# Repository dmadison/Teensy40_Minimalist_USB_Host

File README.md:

# Teensy 4.0 Minimalist USB Host Shield

This repository contains the KiCAD 6 board files for the [Teensy 4.0 minimalist USB host shield](https://www.partsnotincluded.com/teensy-4-0-minimalist-usb-host-shield). The shield is designed to connect to the underside of the Teensy 4.0 board and provide a safe and stable USB-A host port in a small and lightweight size.

The Teensy board needs to be soldered to 0.1" male headers. It can then be mated to the shield with 0.1" female headers and pogo pins, or soldered directly using enamel wire to connect to the data pads on the underside of the board.

For pogo pins, see the [PJRC Teensy 4.0 breakout board](https://www.pjrc.com/breakout-board-for-teensy-4-0/) page for reference. For my own boards I used 12 mm pogo pins purchased from RTLECS on AliExpress.

Generated gerbers and bill of materials can be found on the [releases](../../releases/latest) page.

## License

The KiCAD project files including the schematic, PCB design, symbols, and most footprints are released in the public domain with no rights reserved.

The [Parts Not Included](https://www.partsnotincluded.com/) logo, included on the bottom of the shield, is copyrighted. It may be reproduced as a silkscreen graphic in this project and its derivatives without modification.

Included images are licensed under the [CC BY-NC-ND 4.0 license](https://creativecommons.org/licenses/by-nc-nd/4.0/). Attribution should be to Dave Madison ([@dmadison](https://github.com/dmadison)).

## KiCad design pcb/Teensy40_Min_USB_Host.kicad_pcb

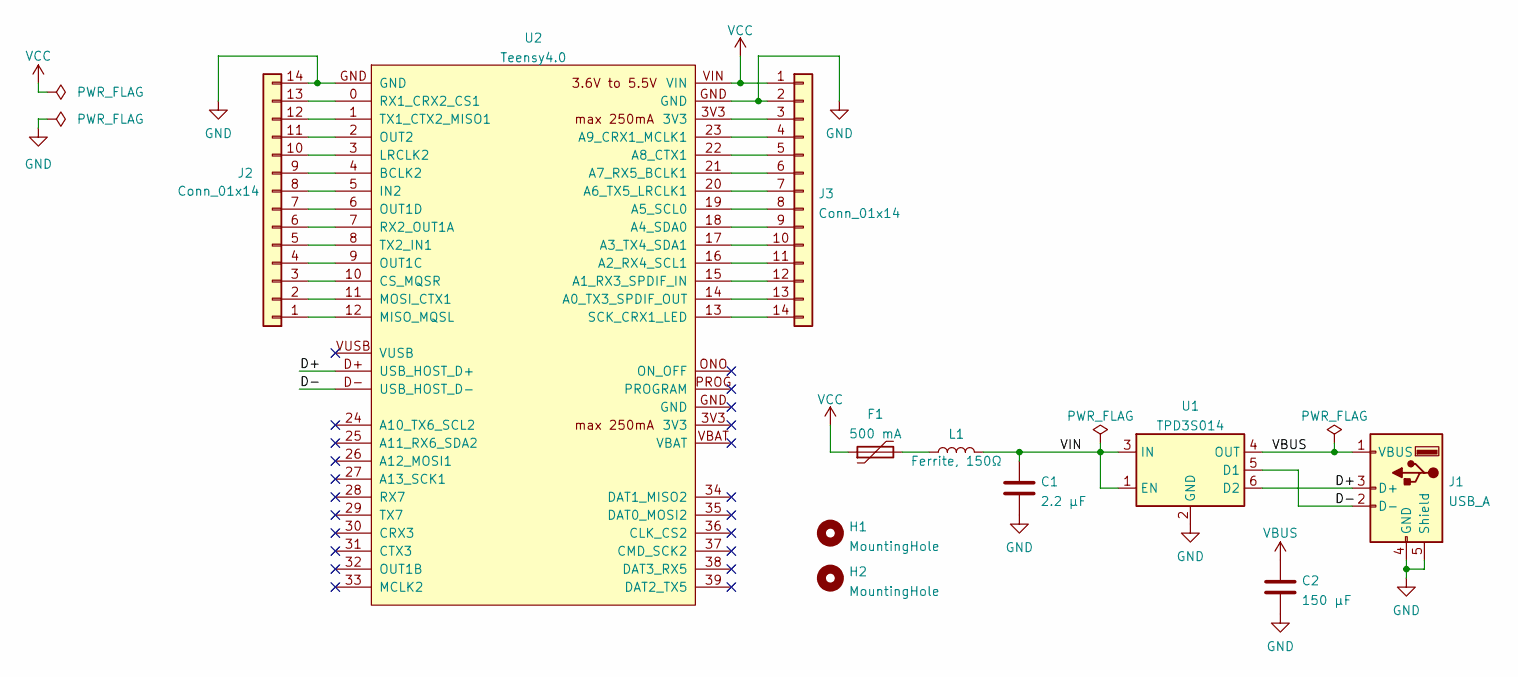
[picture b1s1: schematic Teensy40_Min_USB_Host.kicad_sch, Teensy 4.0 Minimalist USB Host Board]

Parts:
C1: 2.2 µF; C_0805_2012Metric; DigiKey Product Number 445-1420-1-ND - Cut Tape
C2: 150 µF; CP_EIA-3216-10_Kemet-I; DigiKey Product Number 478-6250-1-ND
F1: 500 mA; Fuse_0805_2012Metric; DigiKey Product Number 283-PTS08056V050CT-ND
H1, H2: MountingHole; MountingHole_3.2mm
J1: USB_A; USB_A_Stewart_SS-52100-001_Horizontal; DigiKey Product Number 380-1412-ND
J2, J3: Conn_01x14; PinHeader_1x14_P2.54mm_Vertical; DigiKey Product Number S1011EC-14-ND
L1: Ferrite, 150Ω; L_0805_2012Metric; DigiKey Product Number MH2029-151YCT-ND
U1: TPD3S014; SOT-23-6; DigiKey Product Number 296-44163-1-ND
U2: Teensy4.0; Teensy40_USB; DigiKey Product Number 1568-DEV-15583-ND

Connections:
/D+: J1.3 (D+), U1.6 (D2), U2.D+ (USB_HOST_D+)
/D-: J1.2 (D-), U1.5 (D1), U2.D- (USB_HOST_D-)
/VIN: C1.1, L1.2, U1.1 (EN), U1.3 (IN)
GND: C1.2, C2.2, J1.4 (GND), J1.5 (Shield), J2.14, J3.2, U1.2 (GND), U2.GND
unnamed: F1.2, L1.1
unnamed: J2.1, U2.12 (MISO_MQSL)
unnamed: J2.2, U2.11 (MOSI_CTX1)
unnamed: J2.3, U2.10 (CS_MQSR)
unnamed: J2.4, U2.9 (OUT1C)
unnamed: J2.5, U2.8 (TX2_IN1)
unnamed: J2.6, U2.7 (RX2_OUT1A)
unnamed: J2.7, U2.6 (OUT1D)
unnamed: J2.8, U2.5 (IN2)
unnamed: J2.9, U2.4 (BCLK2)
unnamed: J2.10, U2.3 (LRCLK2)
unnamed: J2.11, U2.2 (OUT2)
unnamed: J2.12, U2.1 (TX1_CTX2_MISO1)
unnamed: J2.13, U2.0 (RX1_CRX2_CS1)
unnamed: J3.3, U2.3V3
unnamed: J3.4, U2.23 (A9_CRX1_MCLK1)
unnamed: J3.5, U2.22 (A8_CTX1)
unnamed: J3.6, U2.21 (A7_RX5_BCLK1)
unnamed: J3.7, U2.20 (A6_TX5_LRCLK1)
unnamed: J3.8, U2.19 (A5_SCL0)
unnamed: J3.9, U2.18 (A4_SDA0)
unnamed: J3.10, U2.17 (A3_TX4_SDA1)
unnamed: J3.11, U2.16 (A2_RX4_SCL1)
unnamed: J3.12, U2.15 (A1_RX3_SPDIF_IN)
unnamed: J3.13, U2.14 (A0_TX3_SPDIF_OUT)
unnamed: J3.14, U2.13 (SCK_CRX1_LED)
VBUS: C2.1, J1.1 (VBUS), U1.4 (OUT)
VCC: F1.1, J3.1, U2.VIN

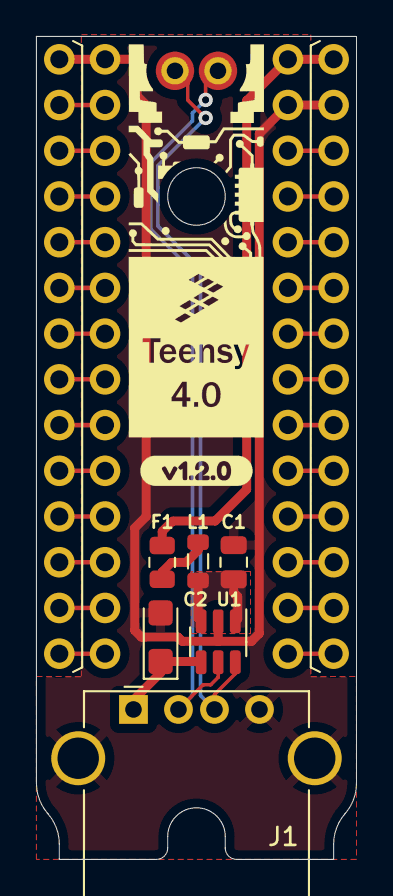
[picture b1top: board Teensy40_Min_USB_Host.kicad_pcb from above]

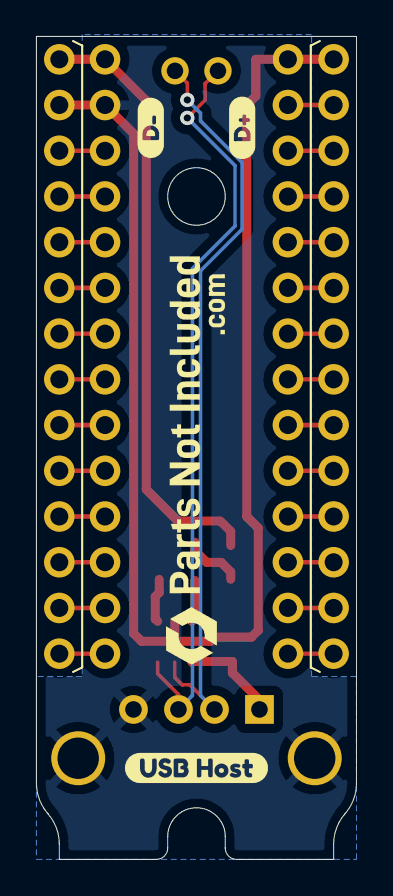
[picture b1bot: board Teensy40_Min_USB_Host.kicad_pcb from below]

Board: 2 copper layers, 17.8 x 45.7 mm, 14 parts (5 on the bottom side), 32 nets.

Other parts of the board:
kibuzzard-61E338B9: G***; kibuzzard-61E338B9
kibuzzard-61E3388A: G***; kibuzzard-61E3388A
kibuzzard-621DEA3B: G***; kibuzzard-621DEA3B
kibuzzard-628AF6F2: G***; kibuzzard-628AF6F2

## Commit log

2022-03-01 Add note about pogo pins to README
2022-03-01 Change fuse footprint
    Use the proper 0805 fuse footprint instead of the 0805 inductor footprint.
2022-03-01 Move board edge back by 0.2"
    Allows space for the USB-A port to integrate into a panel or case.
    With the smaller size, the alignment hole at the USB-A port has been moved to make a half-circle cut at the board edge. This changes the distance between alignment holes from 1.4" to 1.45".
2022-03-01 Move alignment hole back to original position
    This makes the alignment hole position and distance (1.4") the same between v1.0.0 and v1.1.0. For what that's worth.
2022-03-01 Add board version to README image alt tag
2022-05-23 Remove lower portion of Teensy circuit silkscreen
    Making some extra space for the version label, so it's not covered by the USB port.
2022-05-23 Update version footprint to 1.2.0
    This is also now positioned underneath the Teensy instead of underneath the USB port, for visibility whenever the circuit is fully soldered.
2022-05-23 Replace C2 cap with tantalum, 150 uF
    Having some suspected brownout issues with rumble motors using the 100 uF ceramic cap, and I found some documentation from TI that says the USB host output capacitance should be 120 µF at a minimum.
2022-05-23 Update Teensy schematic symbol from lib
    I forgot to update the schematic after updating the library. Committing now to satisfy the ERC check.
2022-05-23 Remove H2 mounting hole
    This semi-circle is now part of the board outline, and the radius (1.6 mm) is large enough for most board houses that a separate drill is not needed.
2022-05-23 Add VBUS label to schematic
    Better than using a local label standalone.
2022-05-23 Shorten and arrange all silkscreen refs
    Making these slightly smaller (0.8 -> 0.7) and aligned straight, both with their components and with each-other.
2022-05-23 Flip current limiter horizontal positions
    This provides much better routing of the VBUS net, which can go directly between U1 and C2 instead of having to route around the USB port pins.
2022-05-23 Add gerbers folder to gitignore
    Gerbers are published with GitHub releases
2022-05-23 Center current limiting circuit block
    "Center" being a rough estimate.
    Man these are huge diffs for such a minor change... those filled zones are no joke.
2022-07-13 Fix PCB edge cut grouping
    Remove redundant groups and add second hole cutout segments.
2022-07-13 Fix malformed board edge fillet
    These curves were not continuous, which created a crossover artifact where they met. This wasn't flagged as an issue because the board area is technically fully enclosed.
    This commit fixes the curve so it's smooth. Note that my 1.2 boards manufactured by OSH Park turned out fine with the malformed edge, so this is mostly just a design-space issue.
